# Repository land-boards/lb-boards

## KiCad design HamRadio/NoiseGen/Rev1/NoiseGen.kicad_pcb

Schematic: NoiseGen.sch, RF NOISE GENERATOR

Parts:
C1: 81PF; C_Rect_L4.0mm_W2.5mm_P2.50mm; MfgPN 1C10Z5U104M050B
C2, C3, C4: 0.01uF; C_Rect_L4.0mm_W2.5mm_P2.50mm; MfgPN 1C10Z5U104M050B
C5: 0.1uF; C_Rect_L4.0mm_W2.5mm_P2.50mm; MfgPN 1C10Z5U104M050B
DZ1, DZ2: 5V; D_DO-34_SOD68_P7.62mm_Horizontal
MTG4: MTG_HOLE; MTG-4-40
Q1, Q2: 2N3904; TO-92_HandSolder
R1, R3, R5, R6: 680; R_Axial_DIN0207_L6.3mm_D2.5mm_P10.16mm_Horizontal
R2: 100; R_Axial_DIN0207_L6.3mm_D2.5mm_P10.16mm_Horizontal
R4: 510; R_Axial_DIN0207_L6.3mm_D2.5mm_P10.16mm_Horizontal
R7: 51; R_Axial_DIN0207_L6.3mm_D2.5mm_P10.16mm_Horizontal
TESTED1: COUPON; TEST_BLK-REAR
TP1, TP2, TP3, TP4: TestPoint; TestPoint_THTPad_2.0x2.0mm_Drill1.0mm

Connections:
/+12V: C5.1, R1.2, R3.2, R5.2, R6.2, TP2.1
/N1: C1.1, DZ1.2 (K), R1.1, R2.2, R3.1
/N2: DZ1.1 (A), Q1.2 (B)
/N3: C2.2, Q1.3 (C), R2.1
/N4: C2.1, Q2.2 (B), R4.1
/N5: C4.2, Q2.3 (C), R7.1
/N6: C3.2, DZ2.2 (K), R5.1, R6.1, R7.2
/RF-OUT: C4.1, TP1.1
GND: C1.2, C3.1, C5.2, Q1.1 (E), Q2.1 (E), TP3.1, TP4.1
unnamed: DZ2.1 (A), R4.2

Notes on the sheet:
GND
+12V

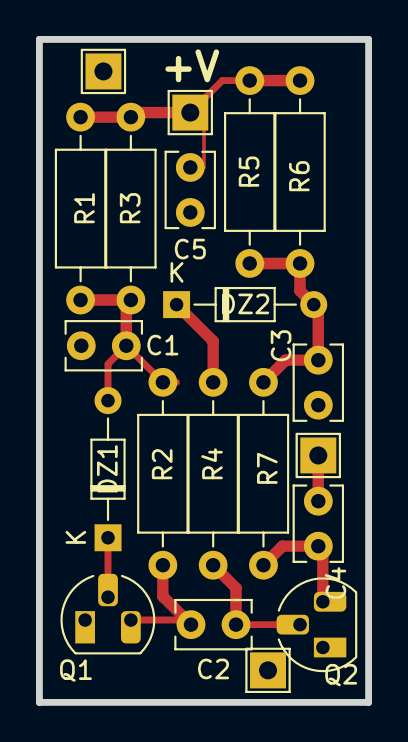
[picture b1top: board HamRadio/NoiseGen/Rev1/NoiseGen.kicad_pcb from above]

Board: 2 copper layers, 18.3 x 36.8 mm, 20 parts (0 on the bottom side), 10 nets.

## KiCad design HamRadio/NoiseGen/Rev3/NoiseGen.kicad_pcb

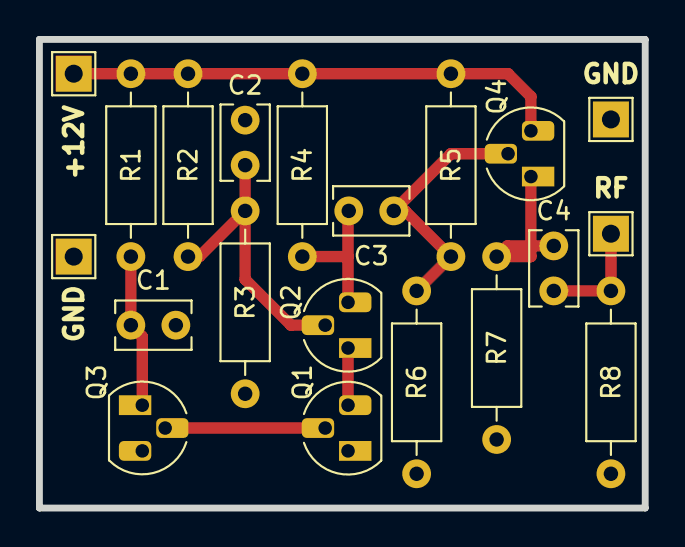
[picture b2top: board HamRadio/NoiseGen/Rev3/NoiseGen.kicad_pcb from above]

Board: 2 copper layers, 33.7 x 26.0 mm, 20 parts (0 on the bottom side), 10 nets.

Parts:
C1, C2, C3, C4: 0.1uF; C_Rect_L4.0mm_W2.5mm_P2.50mm
Q1, Q2, Q3, Q4: 2N3904; TO-92_HandSolder
R1: 470K; R_Axial_DIN0207_L6.3mm_D2.5mm_P10.16mm_Horizontal
R2: 120K; R_Axial_DIN0207_L6.3mm_D2.5mm_P10.16mm_Horizontal
R3: 150K; R_Axial_DIN0207_L6.3mm_D2.5mm_P10.16mm_Horizontal
R4: 560; R_Axial_DIN0207_L6.3mm_D2.5mm_P10.16mm_Horizontal
R5: 30K; R_Axial_DIN0207_L6.3mm_D2.5mm_P10.16mm_Horizontal
R6: 33K; R_Axial_DIN0207_L6.3mm_D2.5mm_P10.16mm_Horizontal
R7, R8: 680; R_Axial_DIN0207_L6.3mm_D2.5mm_P10.16mm_Horizontal
TP1, TP2, TP3, TP4: TestPoint; TestPoint_THTPad_2.0x2.0mm_Drill1.0mm

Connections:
/+12V: Q4.3, R1.2, R2.2, R4.2, R5.2, TP2.1
/N1: C1.1, Q3.1, R1.1
/N2: Q1.2, Q3.2
/N3: C2.1, Q2.2, R2.1, R3.2
/N4: C3.2, Q2.3, R4.1
/N5: C3.1, Q4.2, R5.1, R6.2
/N6: C4.2, Q4.1, R7.2
GND: C1.2, C2.2, Q1.1, R3.1, R6.1, R7.1, R8.1, TP3.1, TP4.1
unnamed: C4.1, R8.2, TP1.1
unnamed: Q1.3, Q2.1

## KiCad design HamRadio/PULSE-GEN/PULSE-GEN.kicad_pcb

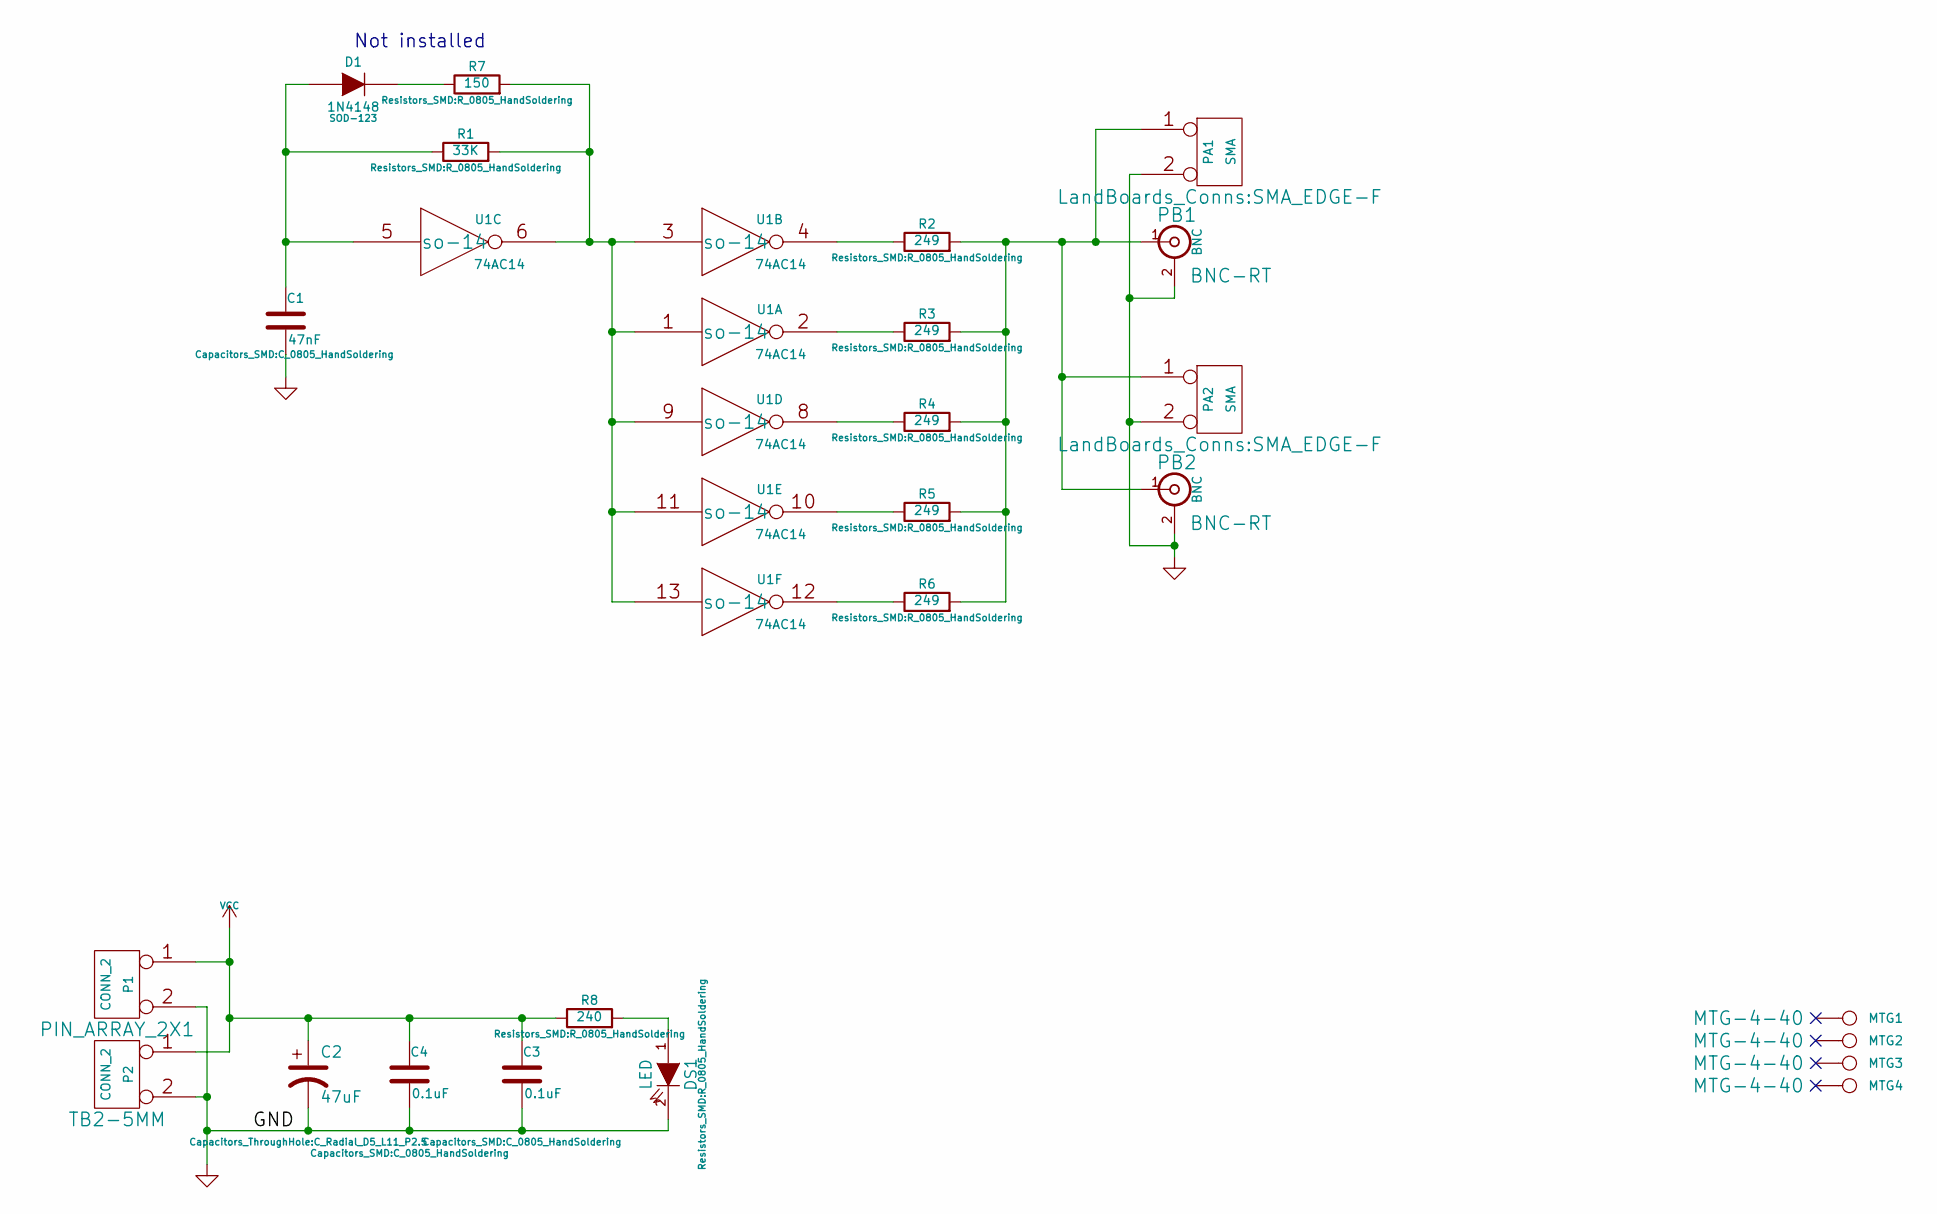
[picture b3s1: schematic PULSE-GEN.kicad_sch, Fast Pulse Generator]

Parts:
C1: 47nF; C_0805_HandSoldering
C2: 47uF; C_Radial_D5_L11_P2.5
C3, C4: 0.1uF; C_0805_HandSoldering
D1: 1N4148; SOD-123
DS1: LED; R_0805_HandSoldering
MTG1, MTG2, MTG3, MTG4: CONN_1; MTG-4-40
P1: CONN_2; PIN_ARRAY_2X1
P2: CONN_2; TB2-5MM
PA1, PA2: SMA; SMA_EDGE-F
PB1, PB2: BNC; BNC-RT; MfgPN 31-5431-10RFX
R1: 33K; R_0805_HandSoldering
R2, R3, R4, R5, R6: 249; R_0805_HandSoldering
R7: 150; R_0805_HandSoldering
R8: 240; R_0805_HandSoldering
U1: 74AC14; so-14; MfgPN SN74AC14DR

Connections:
GND: C1.2, C2.2, C3.2, C4.2, DS1.2 (K), P1.2 (PM), P2.2 (PM), PA1.2 (PM), PA2.2 (PM), PB1.2 (Ext), PB2.2 (Ext), U1.7 (GND)
unnamed: C1.1, D1.1 (A), R1.1, U1.5
unnamed: D1.2 (K), R7.1
unnamed: DS1.1 (A), R8.2
unnamed: PA1.1, PA2.1, PB1.1 (In), PB2.1 (In), R2.2, R3.2, R4.2, R5.2, R6.2
unnamed: R1.2, R7.2, U1.1, U1.3, U1.6, U1.9, U1.11, U1.13
unnamed: R2.1, U1.4
unnamed: R3.1, U1.2
unnamed: R4.1, U1.8
unnamed: R5.1, U1.10
unnamed: R6.1, U1.12
VCC: C2.1, C3.1, C4.1, P1.1, P2.1, R8.1, U1.14 (VCC)

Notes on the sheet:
Not installed

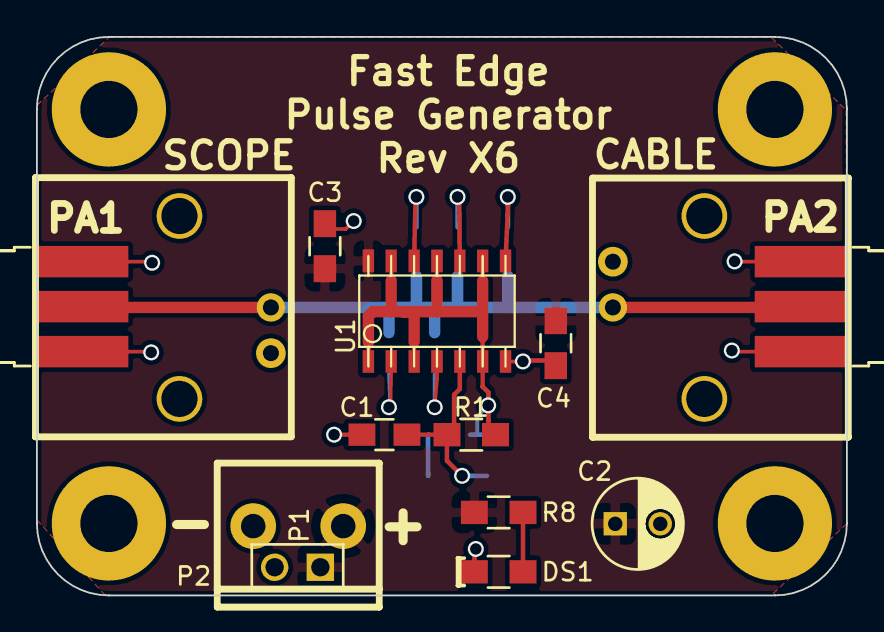
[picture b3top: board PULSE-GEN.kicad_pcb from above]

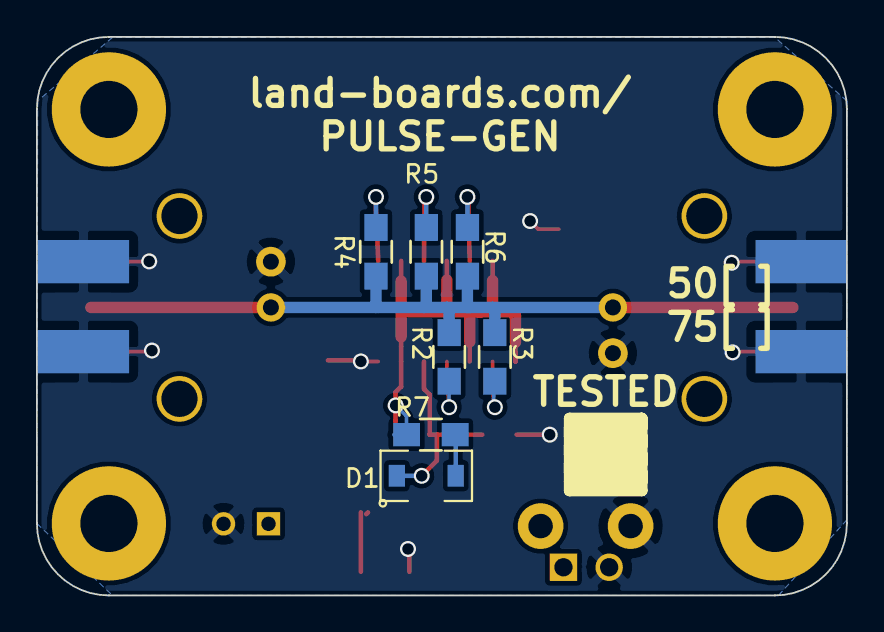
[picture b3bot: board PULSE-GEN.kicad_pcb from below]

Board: 2 copper layers, 45.0 x 31.0 mm, 26 parts (7 on the bottom side), 12 nets.

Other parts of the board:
TESTED: VAL**; TEST_BLK-REAR

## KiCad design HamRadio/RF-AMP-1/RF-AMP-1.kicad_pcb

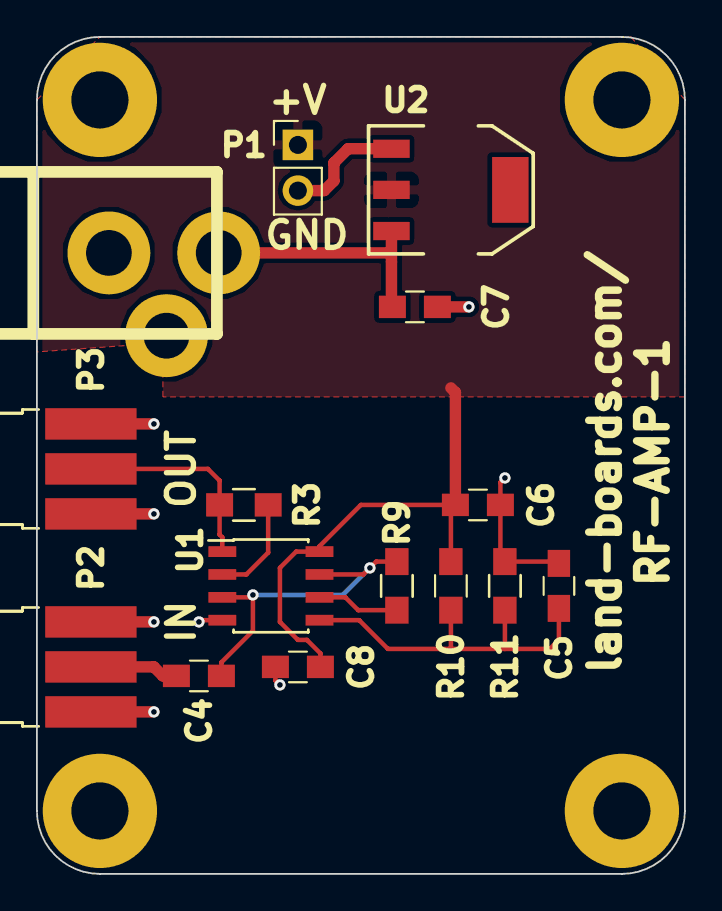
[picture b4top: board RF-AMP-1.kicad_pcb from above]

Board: 2 copper layers, 36.0 x 46.5 mm, 19 parts (0 on the bottom side), 9 nets.

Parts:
C4, C5, C6, C7, C8: 0.1uF; C_0805_HandSoldering
J1: DCJ0202; DCJ-NEW
MTG1, MTG2, MTG3, MTG4: MTG_HOLE; MTG-4-40
P1: CONN_01X02; Pin_Header_Straight_1x02_Pitch2.54mm
P2, P3: BNC; SMA_EDGE-F
R3, R9: 100; R_0805_HandSoldering
R10, R11: 1M; R_0805_HandSoldering
U1: LT1813; SOIC-8_3.9x4.9mm_Pitch1.27mm
U2: AP1117; SOT223

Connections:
/I1+: C4.2, P2.1
GND: C5.2, C6.1, C7.1, C8.1, J1.2, J1.3, P1.2, P2.2, P3.2, R11.1, U1.4, U2.1
unnamed: C4.1, R9.2, U1.3, U1.7
unnamed: C5.1, R10.1, R11.2, U1.5
unnamed: C7.2, J1.1, U2.3
unnamed: P3.1, R3.2, U1.1
unnamed: R3.1, U1.2
unnamed: R9.1, U1.6
VAA: C6.2, C8.2, P1.1, R10.2, U1.8, U2.2

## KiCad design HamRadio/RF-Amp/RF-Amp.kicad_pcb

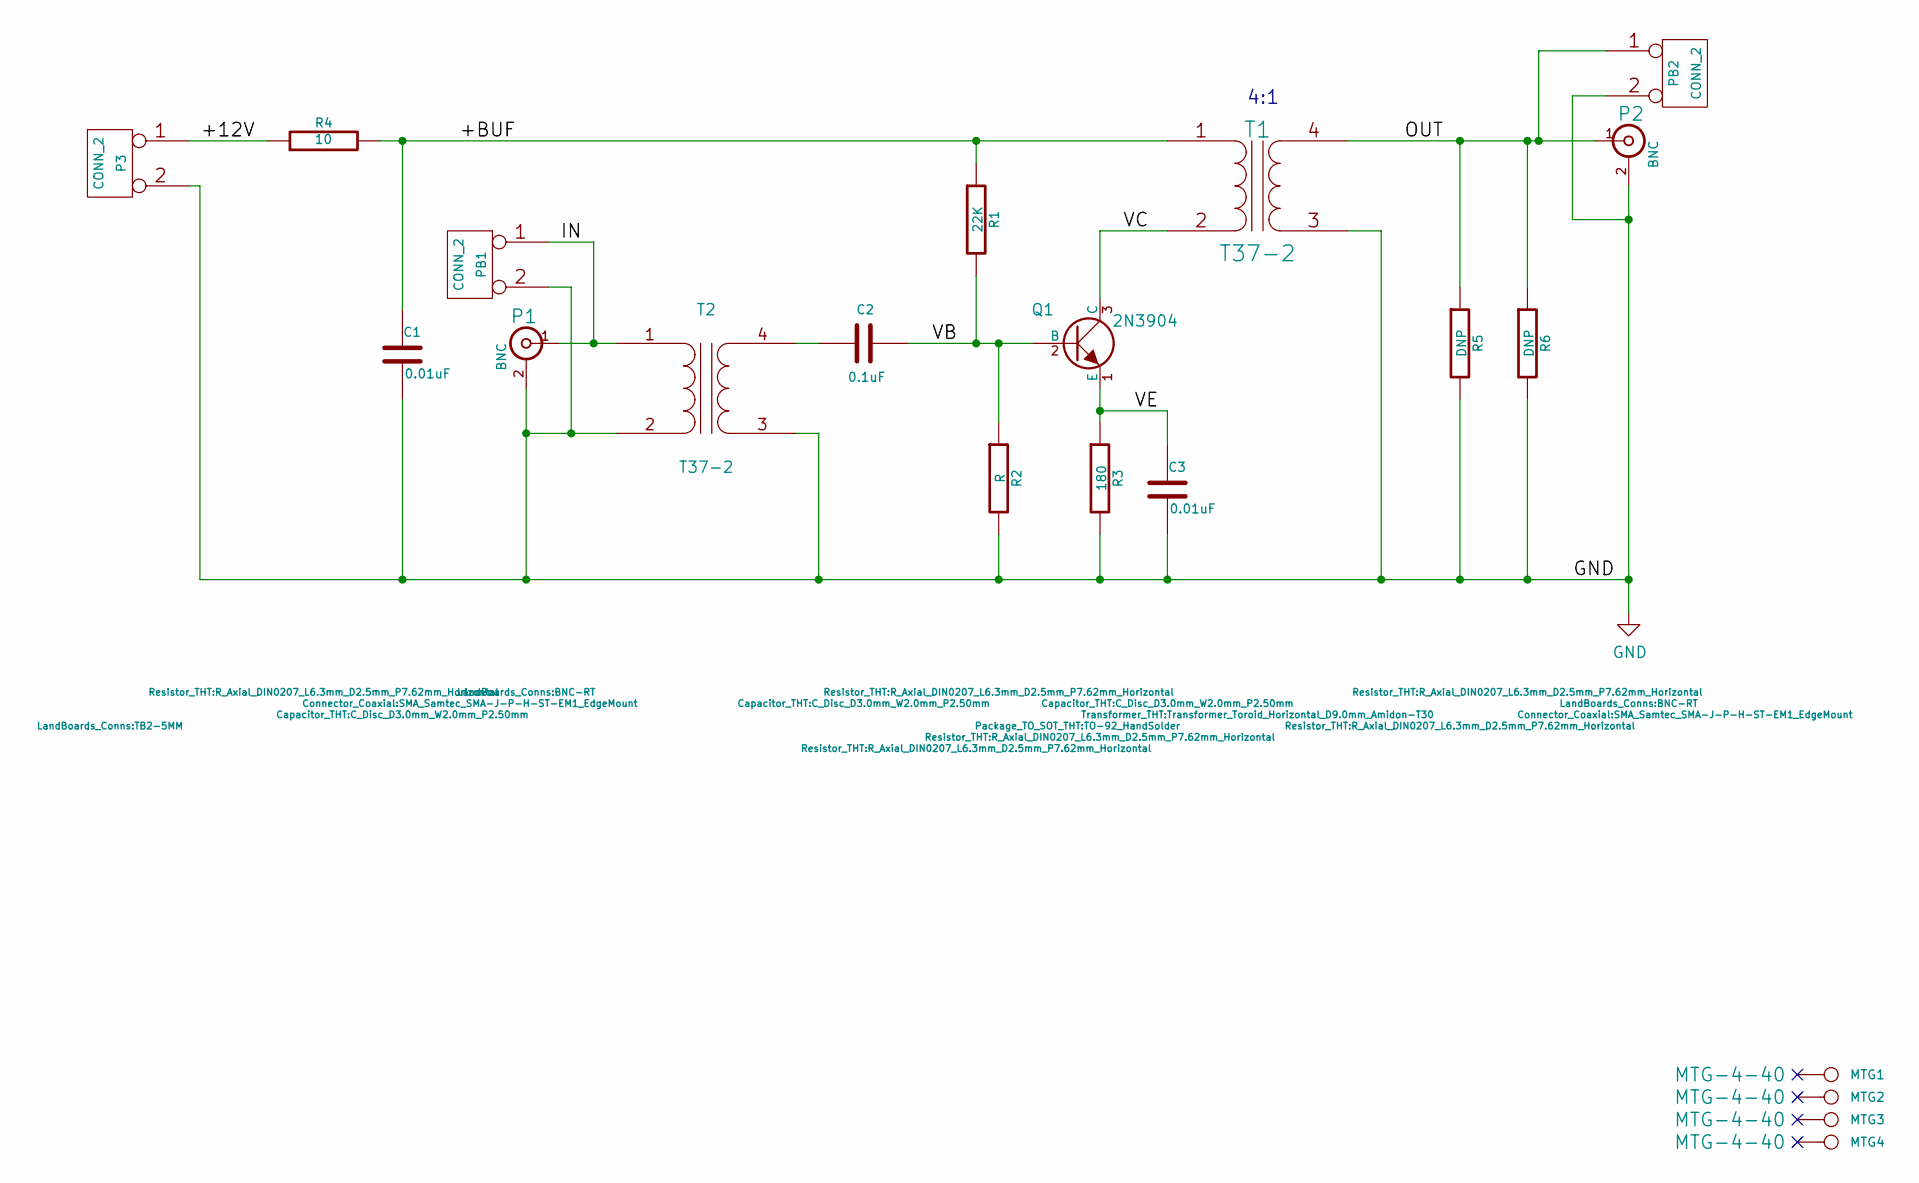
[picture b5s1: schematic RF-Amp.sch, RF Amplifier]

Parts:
C1, C3: 0.01uF; C_Disc_D3.0mm_W2.0mm_P2.50mm
C2: 0.1uF; C_Disc_D3.0mm_W2.0mm_P2.50mm
MTG1, MTG2, MTG3, MTG4: CONN_1; MTG-4-40
P1, P2: BNC; BNC-RT
P3: CONN_2; TB2-5MM
PB1, PB2: CONN_2; SMA_Samtec_SMA-J-P-H-ST-EM1_EdgeMount
Q1: 2N3904; TO-92_HandSolder
R1: 22K; R_Axial_DIN0207_L6.3mm_D2.5mm_P7.62mm_Horizontal
R2: R; R_Axial_DIN0207_L6.3mm_D2.5mm_P7.62mm_Horizontal
R3: 180; R_Axial_DIN0207_L6.3mm_D2.5mm_P7.62mm_Horizontal
R4: 10; R_Axial_DIN0207_L6.3mm_D2.5mm_P7.62mm_Horizontal
R5, R6: DNP; R_Axial_DIN0207_L6.3mm_D2.5mm_P7.62mm_Horizontal
T1, T2: T37-2; Transformer_Toroid_Horizontal_D9.0mm_Amidon-T30

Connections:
/+12V: P3.1, R4.1
/+BUF: C1.1, R1.1, R4.2, T1.1 (AA)
/IN: P1.1 (In), PB1.1, T2.1 (AA)
/OUT: P2.1 (In), PB2.1, R5.1, R6.1, T1.4 (SB)
/VB: C2.2, Q1.2 (B), R1.2, R2.1
/VC: Q1.3 (C), T1.2 (AB)
/VE: C3.1, Q1.1 (E), R3.1
GND: C1.2, C3.2, P1.2 (Ext), P2.2 (Ext), P3.2 (PM), PB1.2 (PM), PB2.2 (PM), R2.2, R3.2, R5.2, R6.2, T1.3 (SA), T2.2 (AB), T2.3 (SA)
unnamed: C2.1, T2.4 (SB)

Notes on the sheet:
4:1

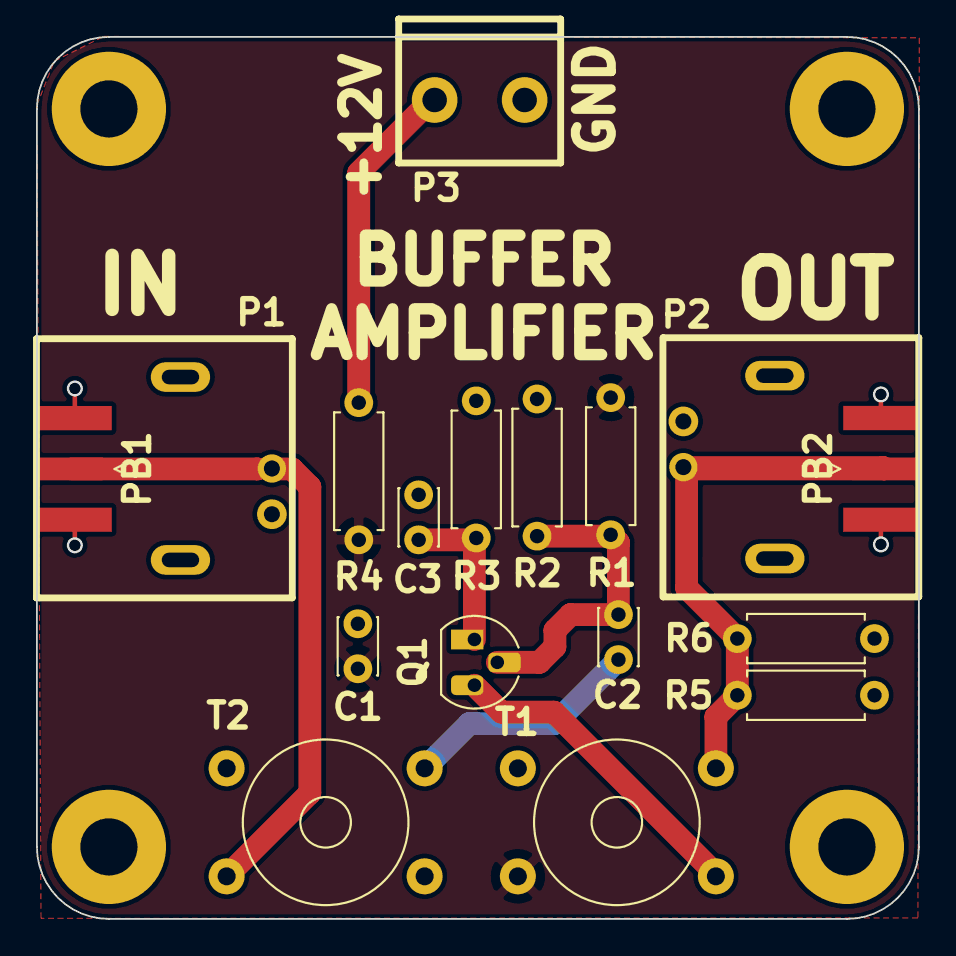
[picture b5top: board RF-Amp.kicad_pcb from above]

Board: 2 copper layers, 49.0 x 49.0 mm, 21 parts (0 on the bottom side), 9 nets.
